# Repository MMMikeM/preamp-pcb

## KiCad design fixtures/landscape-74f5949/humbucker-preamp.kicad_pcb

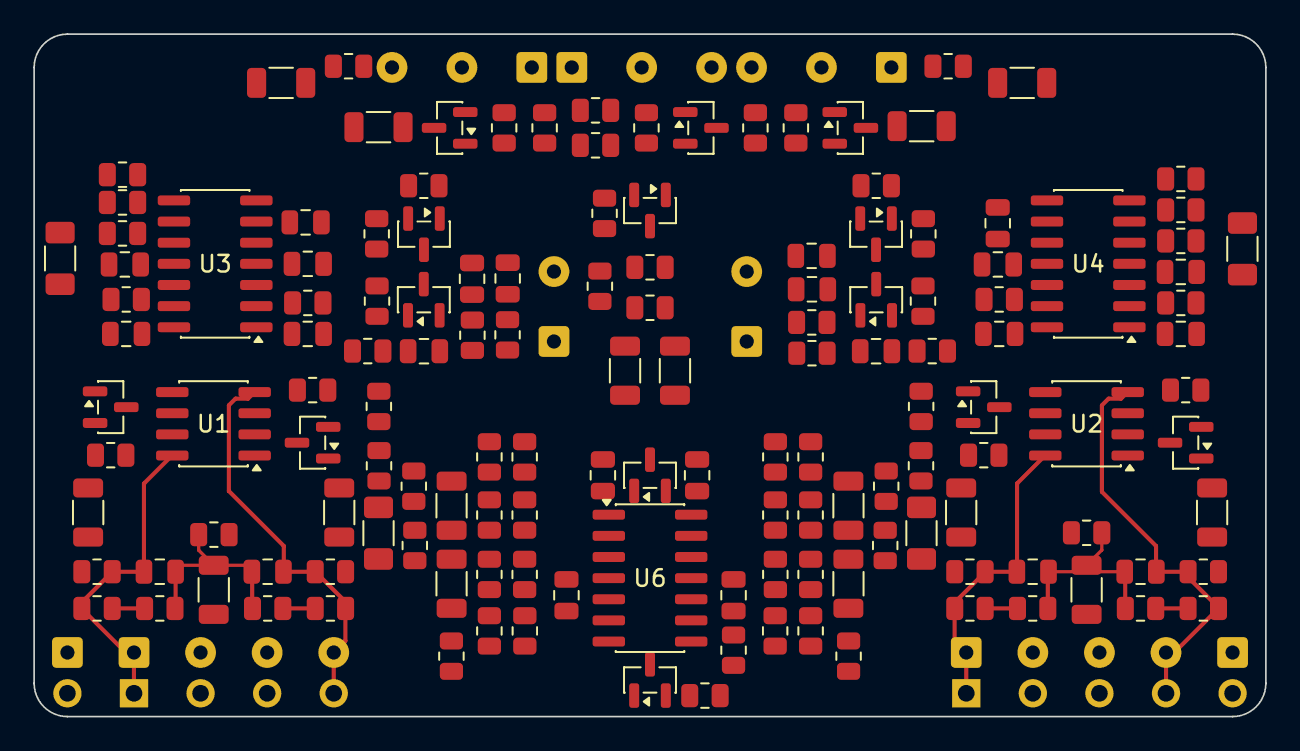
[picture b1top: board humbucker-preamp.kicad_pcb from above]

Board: 4 copper layers, 74.0 x 41.0 mm, 157 parts (0 on the bottom side), 99 nets.

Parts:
C101, C102, C201, C202: 220p; C_0805_2012Metric
C103, C104, C105, C113, C114, C203, C204, C205, C213, C214, C305, C306: 100n; C_1206_3216Metric
C106, C107, C111, C206, C207, C211: 270p; C_0805_2012Metric
C108, C208: 12n; C_0805_2012Metric
C109, C209: 3.3n; C_0805_2012Metric
C110, C210, C303, C304, C307, C308, C309, C310, C311, C312: 1u; C_0805_2012Metric
C112, C212, C301, C302: 47u; C_1206_3216Metric
J1: Battery (+ 0 -); SolderWire-0.25sqmm_1x03_P4.2mm_D0.65mm_OD1.7mm
J2: Blend pot 10k lin; SolderWire-0.25sqmm_1x03_P4.2mm_D0.65mm_OD1.7mm
J3: Output jack (tip, ring, sleeve); SolderWire-0.25sqmm_1x03_P4.2mm_D0.65mm_OD1.7mm
J101, J201: Pickup; SolderWire-0.25sqmm_1x04_P4.0mm_D0.65mm_OD1.7mm
J102, J202: Aux (GA, LINK, LINK, GB); Holes_1x04_P4.00mm
J103, J203: HP pot 500k; SolderWire-0.25sqmm_1x02_P4.2mm_D0.65mm_OD1.7mm
J104, J204: Pickup GND; SolderWire-0.25sqmm_1x01_D0.65mm_OD1.7mm
J105, J205: Aux GND; Holes_1x01
Q101, Q102, Q104, Q201, Q202, Q204, Q301, Q304: BC860C; SOT-23
Q103, Q203, Q302, Q303, Q305: BC850C; SOT-23
R101, R102, R103, R104, R128, R129, R130, R131, R132, R133, R134, R135, R201, R202, R203, R204, R228, R229, R230, R231, R232, R233, R234, R235: 20M; R_0805_2012Metric
R105, R106, R136, R205, R206, R236, R302, R303, R310: 330k; R_0805_2012Metric
R107, R108, R112, R115, R116, R121, R125, R207, R208, R212, R215, R216, R221, R225, R313: 1k; R_0805_2012Metric
R109, R209: 330R; R_1206_3216Metric_Pad1.30x1.75mm_HandSolder
R110, R111, R118, R126, R210, R211, R218, R226: 2k; R_0805_2012Metric
R113, R114, R119, R120, R124, R213, R214, R219, R220, R224, R307, R308, R309, R312: 15k; R_0805_2012Metric
R117, R217: 5.6k; R_1206_3216Metric_Pad1.30x1.75mm_HandSolder
R122, R127, R222, R227, R305, R311: 47k; R_0805_2012Metric
R123, R223, R301, R304, R306: 2.2M; R_0805_2012Metric
U1, U2: JFE2140; SOIC-8_3.9x4.9mm_P1.27mm
U3, U4: TLV9104; SOIC-14_3.9x8.7mm_P1.27mm
U5: REF3312; SOT-23
U6: TLV9144; SOIC-14_3.9x8.7mm_P1.27mm

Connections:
/BAT+: J1.1, Q301.2, R301.1
/BAT-: J1.3, Q302.2, Q303.2, R304.2, R306.2
/Bridge/BO: C211.2, C212.1, R225.1, U4.8
/Bridge/CLD: C205.2, R217.2, R218.1, R219.1
/Bridge/DA: Q201.3, R215.1, U2.2, U4.2
/Bridge/DB: Q202.3, R216.1, U2.6, U4.13
/Bridge/GA: C201.1, J201.1, J202.1, R201.1, R205.2, U2.8
/Bridge/GA_M: R201.2, R202.1
/Bridge/GB: C202.2, J201.4, J202.4, R203.2, R206.1, U2.4
/Bridge/GB_M: R203.1, R204.2
/Bridge/LINK: J201.2, J201.3, J202.2, J202.3
/Bridge/OA: C206.2, R210.1, R211.2, R228.1, R229.1, U4.1
/Bridge/OB: C207.2, R212.1, R217.1, R221.1, U4.14
/Bridge/OBN: C204.1, R220.2, U4.7
/Bridge/SA: R207.1, R209.2, R210.2, R232.1, R233.1, U2.1
/Bridge/SB: R208.1, R211.1, R212.2, U2.5
/Bridge/SO: R231.2, R236.1, U6.14
/Bridge/SVN: C213.1, R228.2, R229.2, U6.13
/Bridge/SVN_I: C213.2, R230.1
/Bridge/SVN_R: R230.2, R231.1
/Bridge/SVP: C214.1, R232.2, R233.2, U6.12
/Bridge/SVP_I: C214.2, R234.1
/Bridge/SVP_R: R234.2, R235.1
/Bridge/VB: C201.2, C202.1, C203.1, R202.2, R204.1, R236.2
/Neck/BO: C111.2, C112.1, R125.1, U3.7
/Neck/CLD: C105.2, R117.2, R118.1, R119.1
/Neck/DA: Q101.3, R115.1, U1.2, U3.2
/Neck/DB: Q102.3, R116.1, U1.6, U3.13
/Neck/GA: C101.1, J101.1, J102.1, R101.1, R105.2, U1.8
/Neck/GA_M: R101.2, R102.1
/Neck/GB: C102.2, J101.4, J102.4, R103.2, R106.1, U1.4
/Neck/GB_M: R103.1, R104.2
/Neck/LINK: J101.2, J101.3, J102.2, J102.3
/Neck/OA: C106.2, R110.1, R111.2, R128.1, R129.1, U3.1
/Neck/OB: C107.2, R112.1, R117.1, R121.1, U3.14
/Neck/OBN: C104.1, R120.2, U3.8
/Neck/SA: R107.1, R109.2, R110.2, R132.1, R133.1, U1.1
/Neck/SB: R108.1, R111.1, R112.2, U1.5
/Neck/SO: R131.2, R136.1, U6.1
/Neck/SVN: C113.1, R128.2, R129.2, U6.2
/Neck/SVN_I: C113.2, R130.1
/Neck/SVN_R: R130.2, R131.1
/Neck/SVP: C114.1, R132.2, R133.2, U6.3
/Neck/SVP_I: C114.2, R134.1
/Neck/SVP_R: R134.2, R135.1
/Neck/VB: C101.2, C102.1, C103.1, R102.2, R104.1, R136.2
/OUT_BR: C212.2, J2.3, R227.1
/OUT_NK: C112.2, J2.1, R127.1
/RING: J3.2, R303.1, R305.1
/TIP: J3.1, R313.2
/VR: C303.1, U5.2, U6.5
GND: C103.2, C109.2, C110.2, C203.2, C209.2, C210.2, C301.2, C302.1, C304.1, C307.2, C308.1, C309.2, C310.1, C311.2, C312.1, J1.2, J3.3, J104.1, J105.1, J204.1, J205.1, R107.2, R118.2, R123.2, R127.2, R135.2, R207.2, R218.2, R223.2, R227.2, R235.2, U3.10, U4.5, U5.1, U6.10
unnamed: C104.2, R105.1
unnamed: C105.1, R106.2
unnamed: C106.1, R115.2
unnamed: C107.1, R116.2
unnamed: C108.1, R121.2
unnamed: C204.2, R205.1
unnamed: C205.1, R206.2
unnamed: C206.1, R215.2
unnamed: C207.1, R216.2
unnamed: C208.1, R221.2
unnamed: J2.2, R313.1
unnamed: J103.1, R122.2
unnamed: C110.1, J103.2
unnamed: J203.1, R222.2
unnamed: C210.1, J203.2
unnamed: Q101.2, R113.2
unnamed: Q102.2, R114.2
unnamed: C108.2, C109.1, Q103.1, R122.1, R123.1
unnamed: C111.1, Q103.3, Q104.3, U3.6
unnamed: Q103.2, R126.2
unnamed: Q104.2, R124.2
unnamed: Q201.2, R213.2
unnamed: Q202.2, R214.2
unnamed: C208.2, C209.1, Q203.1, R222.1, R223.1
unnamed: C211.1, Q203.3, Q204.3, U4.9
unnamed: Q203.2, R226.2
unnamed: Q204.2, R224.2
unnamed: Q301.1, R301.2, R302.1
unnamed: Q302.1, R303.2, R304.1
unnamed: Q302.3, R302.2
unnamed: Q303.1, R305.2, R306.1
unnamed: Q304.2, R308.2
unnamed: Q305.1, U6.7
unnamed: Q305.2, R311.1, U6.6
unnamed: R108.2, R109.1
unnamed: R125.2, R126.1
unnamed: R208.2, R209.1
unnamed: R225.2, R226.1
unnamed: R307.2, R308.1
unnamed: R311.2, R312.1
unnamed: R119.2, R120.1, U3.9
unnamed: R219.2, R220.1, U4.6
unnamed: U6.8, U6.9
PB: C305.2, Q101.1, Q102.1, Q104.1, Q201.1, Q202.1, Q204.1, Q304.1, Q304.3, R309.1, R310.1
REF: C306.2, Q305.3, R309.2, R310.2, U3.3, U3.5, U3.12, U4.3, U4.10, U4.12
V+: C301.1, C305.1, C306.1, C307.1, C309.1, C311.1, Q301.3, R113.1, R114.1, R124.1, R213.1, R214.1, R224.1, R307.1, U1.3, U2.3, U3.4, U4.4, U6.4
V-: C302.2, C303.2, C304.2, C308.2, C310.2, C312.2, Q303.3, R312.2, U1.7, U2.7, U3.11, U4.11, U5.3, U6.11
